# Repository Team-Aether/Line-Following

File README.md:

# Line-Following

### Folder description
|Folder | Description|
|---|---|
|<strong>Firmware</strong>|Contains code to control the line following robot.|
|<strong>Hardware</strong>|Contains schematics and corresponding printec circuit board designs for the line follwing part|

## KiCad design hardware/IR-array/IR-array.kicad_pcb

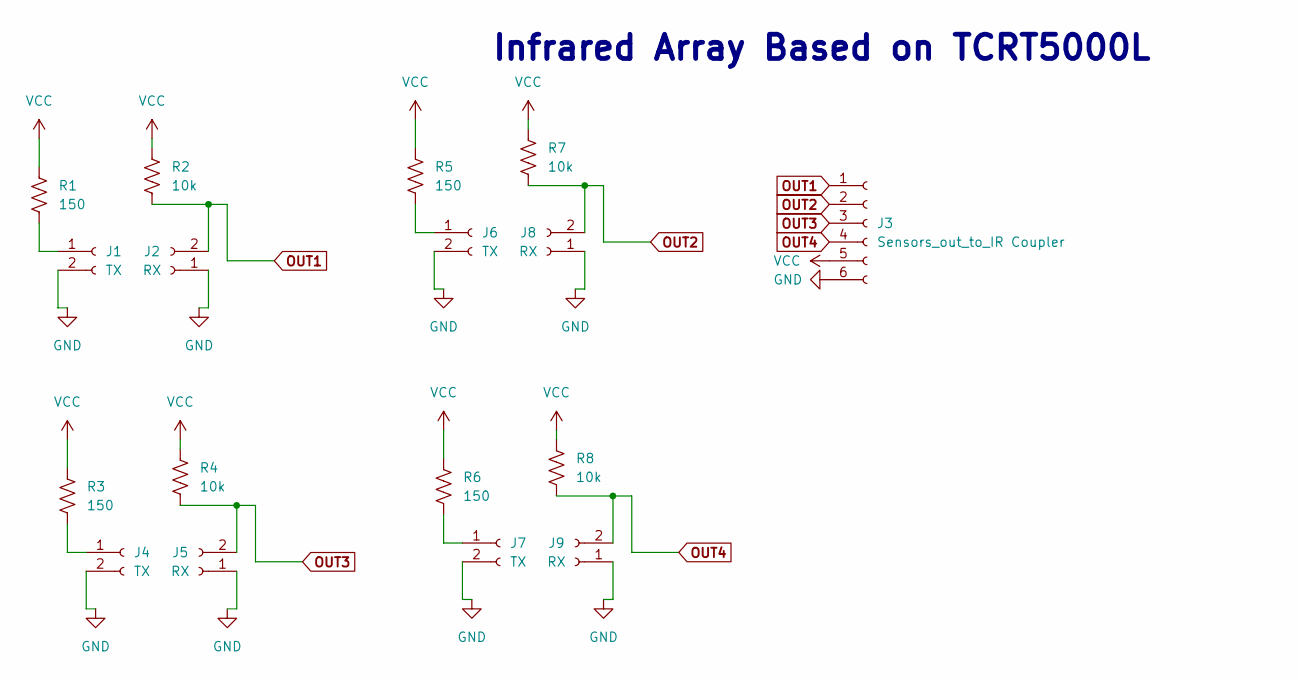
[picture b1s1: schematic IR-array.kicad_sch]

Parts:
J1, J4, J6, J7: TX; PinHeader_1x02_P2.54mm_Vertical
J2, J5, J8, J9: RX; PinHeader_1x02_P2.54mm_Vertical
J3: Sensors_out_to_IR Coupler; PinHeader_1x06_P2.54mm_Vertical
R1, R3, R5, R6: 150; R_Axial_DIN0207_L6.3mm_D2.5mm_P10.16mm_Horizontal
R2, R4, R7, R8: 10k; R_Axial_DIN0207_L6.3mm_D2.5mm_P10.16mm_Horizontal

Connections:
GND: J1.2, J2.1, J3.6, J4.2, J5.1, J6.2, J7.2, J8.1, J9.1
unnamed: J1.1, R1.2
unnamed: J4.1, R3.2
unnamed: J6.1, R5.2
unnamed: J7.1, R6.2
OUT1: J2.2, J3.1, R2.2
OUT2: J3.2, J8.2, R7.2
OUT3: J3.3, J5.2, R4.2
OUT4: J3.4, J9.2, R8.2
VCC: J3.5, R1.1, R2.1, R3.1, R4.1, R5.1, R6.1, R7.1, R8.1

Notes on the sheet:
Infrared Array Based on TCRT5000L

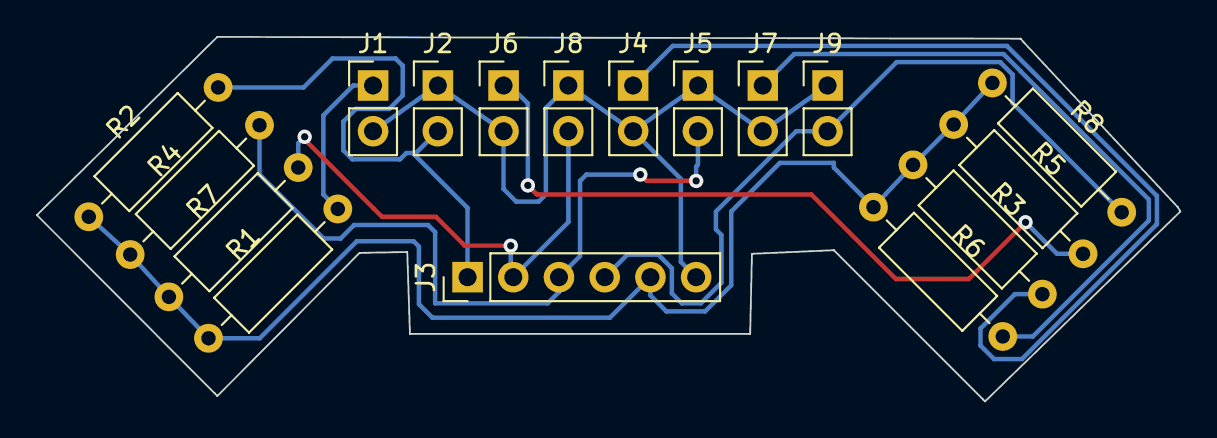
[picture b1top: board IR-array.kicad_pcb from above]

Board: 2 copper layers, 63.5 x 20.2 mm, 17 parts (0 on the bottom side), 10 nets.

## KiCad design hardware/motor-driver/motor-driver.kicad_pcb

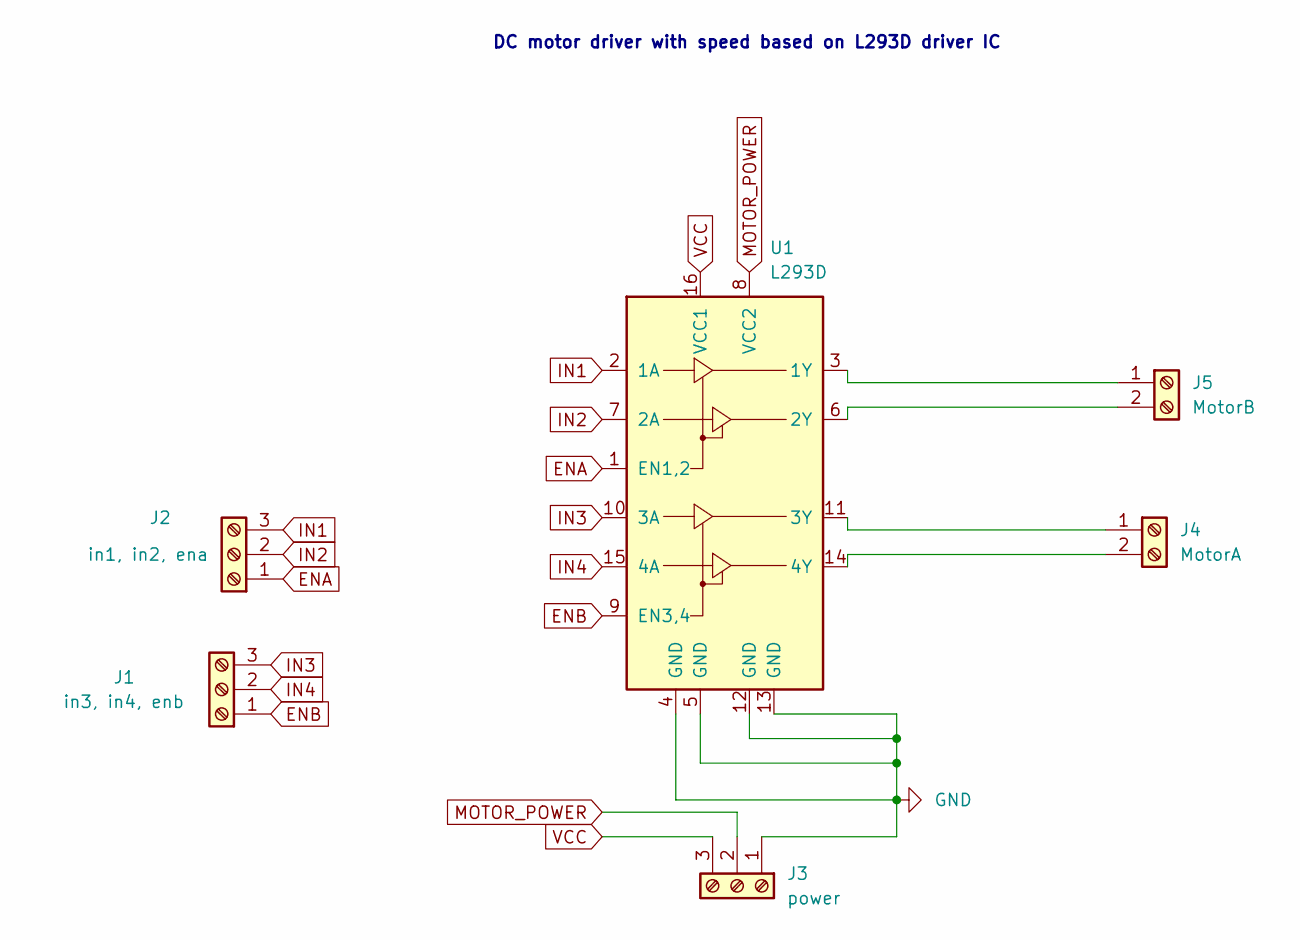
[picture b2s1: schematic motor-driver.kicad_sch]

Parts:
J1: in3, in4, enb; TerminalBlock_Altech_AK300-3_P5.00mm
J2: in1, in2, ena; TerminalBlock_Altech_AK300-3_P5.00mm
J3: power; TerminalBlock_Altech_AK300-3_P5.00mm
J4: MotorA; TerminalBlock_Altech_AK300-2_P5.00mm
J5: MotorB; TerminalBlock_Altech_AK300-2_P5.00mm
U1: L293D; DIP-16_W7.62mm

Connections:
ENA: J2.1, U1.1 (EN1,2)
ENB: J1.1, U1.9 (EN3,4)
GND: J3.1, U1.4 (GND), U1.5 (GND), U1.12 (GND), U1.13 (GND)
IN1: J2.3, U1.2 (1A)
IN2: J2.2, U1.7 (2A)
IN3: J1.3, U1.10 (3A)
IN4: J1.2, U1.15 (4A)
MOTOR_POWER: J3.2, U1.8 (VCC2)
unnamed: J4.1, U1.11 (3Y)
unnamed: J4.2, U1.14 (4Y)
unnamed: J5.1, U1.3 (1Y)
unnamed: J5.2, U1.6 (2Y)
VCC: J3.3, U1.16 (VCC1)

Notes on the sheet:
DC motor driver with speed based on L293D driver IC

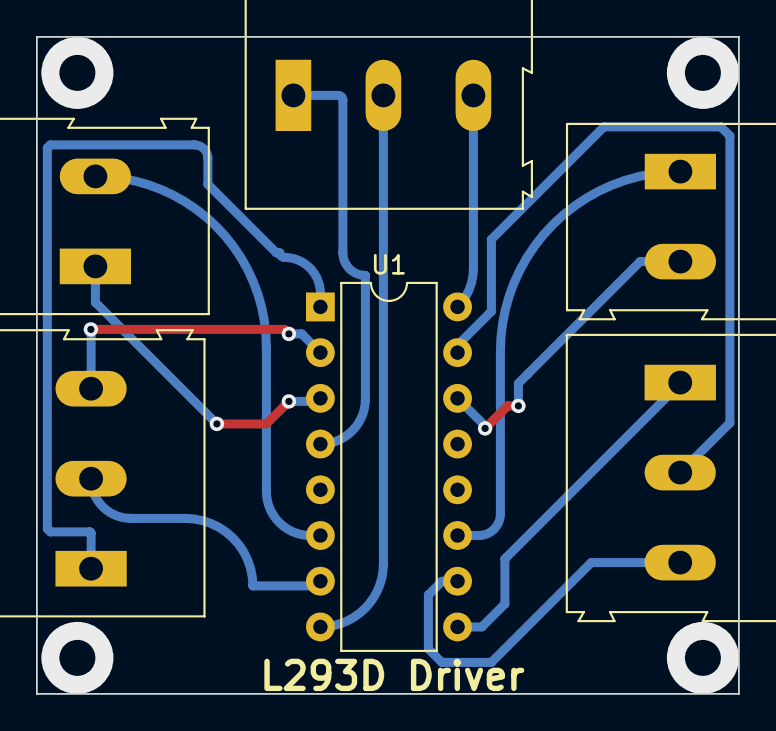
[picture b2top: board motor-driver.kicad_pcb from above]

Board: 2 copper layers, 39.0 x 36.5 mm, 6 parts (0 on the bottom side), 13 nets.

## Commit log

2022-09-21 added properties
2022-09-21 added: folders and line follower code
2022-10-05 added: motor driver and ir array designs
